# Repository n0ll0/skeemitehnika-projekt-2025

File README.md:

# skeemitehnika-projekt-2025

This repository contains the project files for the Skeemitehnika G11 course project "Arduino Nano digisisendi laiendus" & at TTÜ. The project involves designing and implementing an extension for the Arduino Nano to enhance its digital input capabilities.

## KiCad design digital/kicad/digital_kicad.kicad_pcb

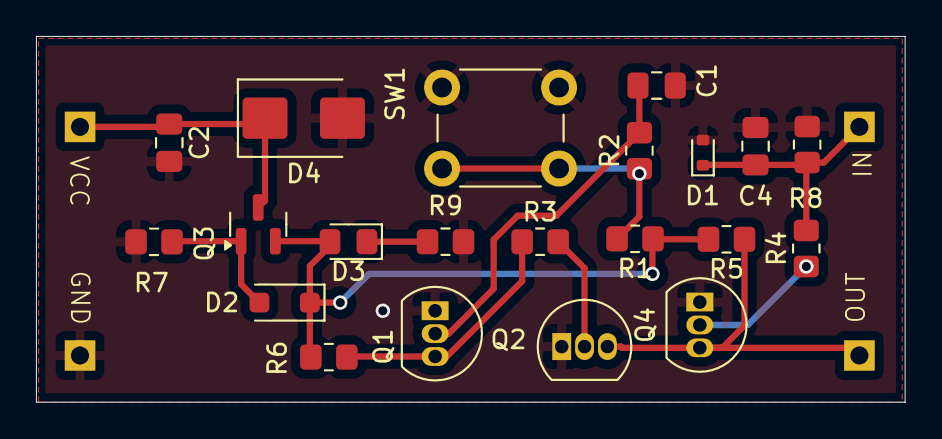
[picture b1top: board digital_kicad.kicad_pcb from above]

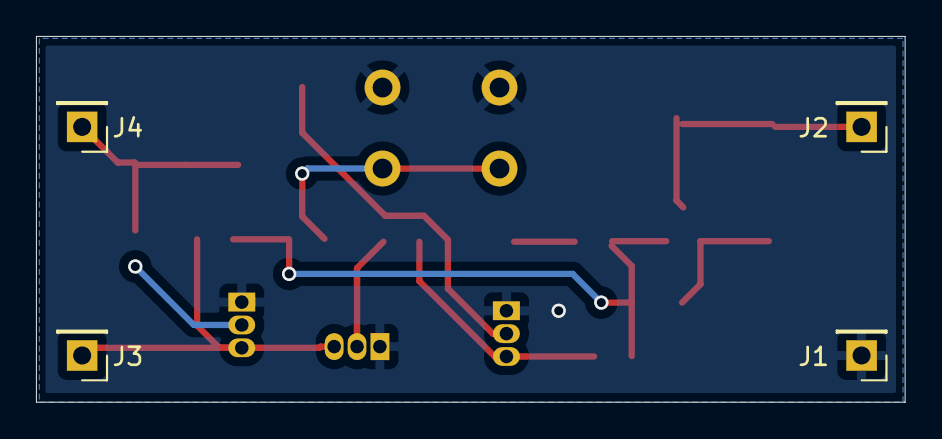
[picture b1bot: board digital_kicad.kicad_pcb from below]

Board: 2 copper layers, 48.3 x 20.3 mm, 25 parts (4 on the bottom side), 12 nets.

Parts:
C1, C4: 1u; C_0805_2012Metric_Pad1.18x1.45mm_HandSolder
C2: 0.1u; C_0805_2012Metric_Pad1.18x1.45mm_HandSolder
D1: ESD5Zxx; D_SOD-523
D2: BZT52Bxx; D_SOD-123F
D3: LED; LED_0805_2012Metric_Pad1.15x1.40mm_HandSolder
D4: SM6T18A; D_SMB
J1, J2, J3, J4: Conn_01x01_Pin; PinHeader_1x01_P2.54mm_Vertical
Q1, Q2, Q4: 2N3904; TO-92_Inline
Q3: FDN340P; SOT-23
R1, R2, R3, R4: 10k; R_0805_2012Metric_Pad1.20x1.40mm_HandSolder
R5, R6: 4.7k; R_0805_2012Metric_Pad1.20x1.40mm_HandSolder
R7: 100k; R_0805_2012Metric_Pad1.20x1.40mm_HandSolder
R8: 33k; R_0805_2012Metric_Pad1.20x1.40mm_HandSolder
R9: 1k; R_0805_2012Metric_Pad1.20x1.40mm_HandSolder
SW1: SW_SPST; SW_PUSH_6mm

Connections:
+5V: D2.1 (K), D3.2 (A), Q3.2 (S), R1.1, R5.2, R6.2
/A: Q4.2 (B), R4.1
/DC_IN: C2.1, D4.1 (A1), J2.1, Q3.3 (D)
/DIG_IN: C4.1, D1.1 (K), J4.1, R4.2, R8.2
/OUT: J3.1, Q2.3 (C), Q4.3 (C), R5.1
/SW: R1.2, R2.1, SW1.1 (A)
/inv. SW: Q1.3 (C), R3.1, R6.1
GND: C1.2, C2.2, C4.2, D1.2 (A), D4.2 (A2), J1.1, Q1.1 (E), Q2.1 (E), Q4.1 (E), R7.1, R8.1, R9.1, SW1.2 (B)
unnamed: D2.2 (A), Q3.1 (G), R7.2
unnamed: D3.1 (K), R9.2
unnamed: C1.1, Q1.2 (B), R2.2
unnamed: Q2.2 (B), R3.2

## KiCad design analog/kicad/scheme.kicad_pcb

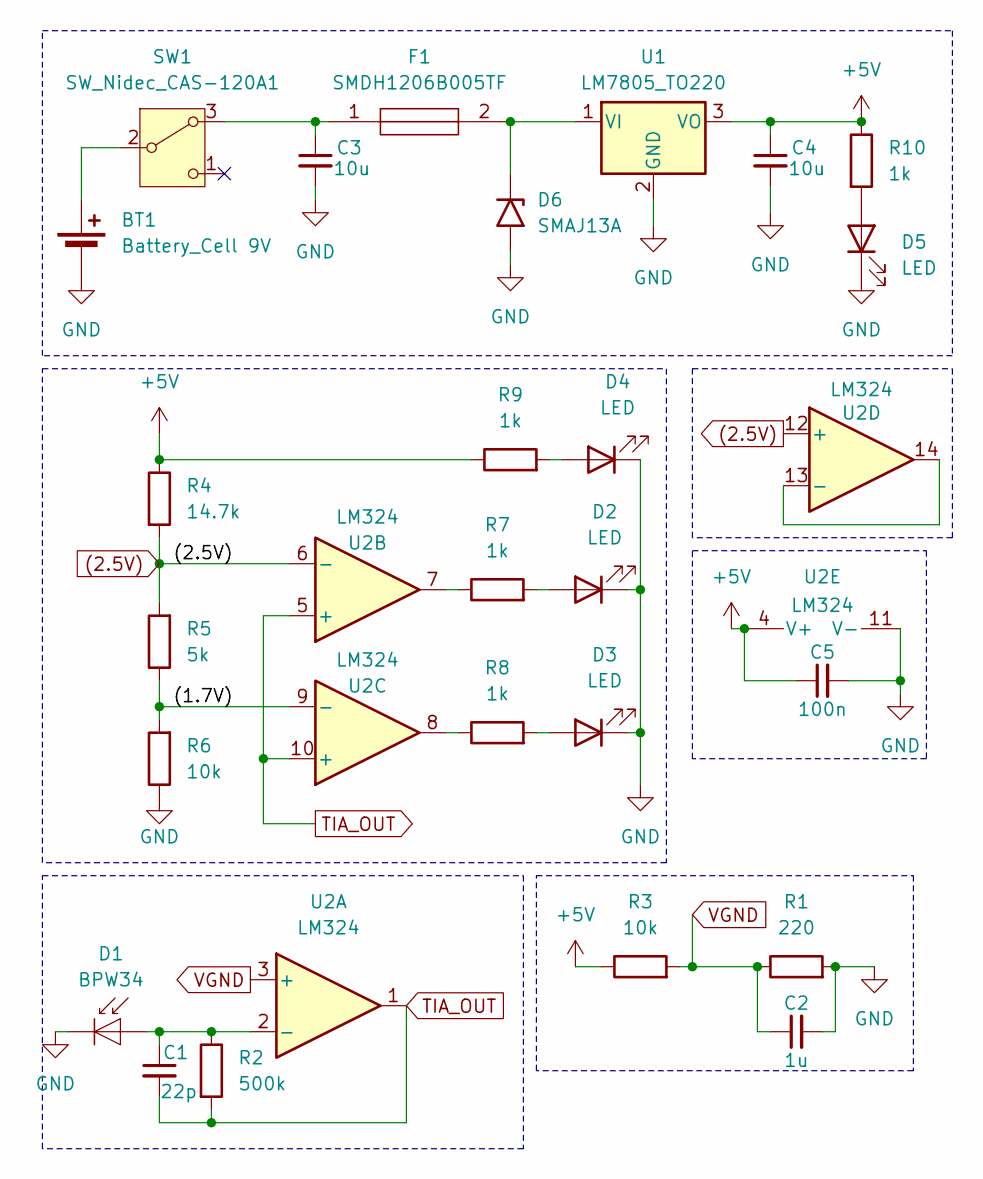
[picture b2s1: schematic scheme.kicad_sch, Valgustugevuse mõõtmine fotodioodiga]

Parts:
BT1: Battery_Cell 9V; BatteryHolder_Eagle_12BH611-GR
C1: 22p; C_0805_2012Metric
C2: 1u; C_0805_2012Metric
C3, C4: 10u; C_0805_2012Metric
C5: 100n; C_0805_2012Metric
D1: BPW34; Osram_DIL2_4.3x4.65mm_P5.08mm
D2, D3, D4: LED; LED_D5.0mm_Horizontal_O1.27mm_Z3.0mm
D5: LED; LED_0805_2012Metric
D6: SMAJ13A; D_SMA
F1: SMDH1206B005TF; R_1206_3216Metric; Manufacturer_Part_Number SMDH1206B005TF
R1: 220; R_0805_2012Metric
R2: 500k; R_0805_2012Metric
R3, R6: 10k; R_0805_2012Metric
R4: 14.7k; R_0805_2012Metric
R5: 5k; R_0805_2012Metric
R7, R8, R9, R10: 1k; R_0805_2012Metric
SW1: SW_Nidec_CAS-120A1; Nidec_Copal_CAS-120A
U1: LM7805_TO220; TO-220-3_Vertical
U2: LM324; DIP-14_W7.62mm_SMDSocket_SmallPads

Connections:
(2.5V): R4.2, R5.2, U2.6 (-), U2.12 (+)
+5V: C4.1, C5.1, R3.1, R4.1, R9.1, R10.1, U1.3 (VO), U2.4 (V+)
/(1.7V): R5.1, R6.2, U2.9 (-)
GND: BT1.2 (-), C2.2, C3.2, C4.2, C5.2, D1.1 (K), D2.1 (K), D3.1 (K), D4.1 (K), D5.1 (K), D6.2 (A2), R1.2, R6.1, U1.2 (GND), U2.11 (V-)
unnamed: BT1.1 (+), SW1.2 (B)
unnamed: C1.1, D1.2 (A), R2.1, U2.2 (-)
unnamed: D2.2 (A), R7.2
unnamed: D3.2 (A), R8.2
unnamed: D4.2 (A), R9.2
unnamed: D5.2 (A), R10.2
unnamed: D6.1 (A1), F1.2, U1.1 (VI)
unnamed: R7.1, U2.7
unnamed: R8.1, U2.8
unnamed: C3.1, F1.1, SW1.3 (A)
unnamed: U2.13 (-), U2.14
TIA_OUT: C1.2, R2.2, U2.1, U2.5 (+), U2.10 (+)
VGND: C2.1, R1.1, R3.2, U2.3 (+)

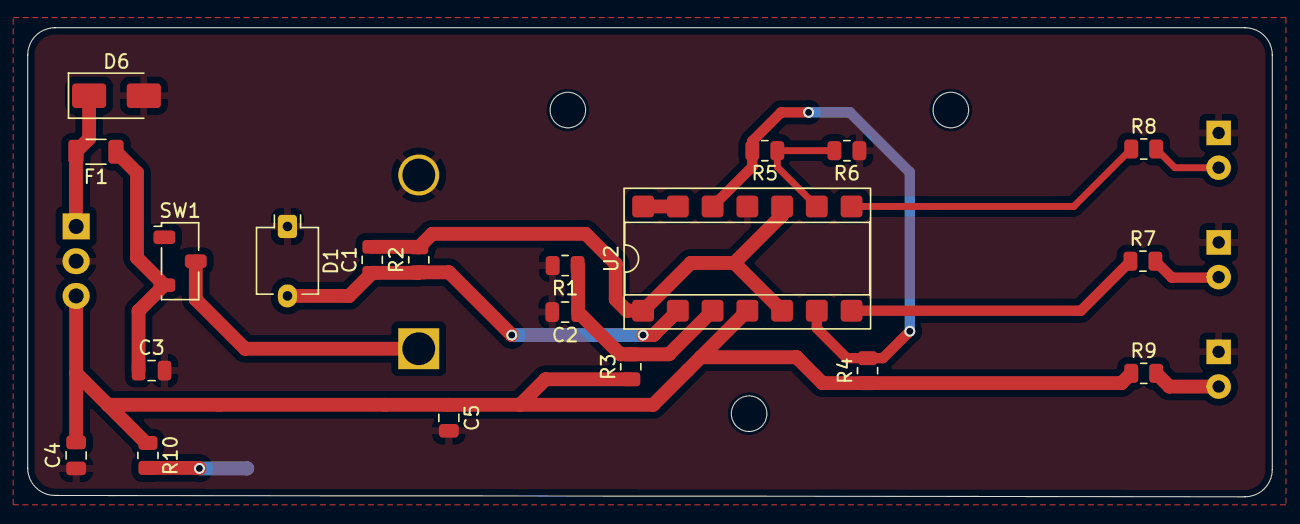
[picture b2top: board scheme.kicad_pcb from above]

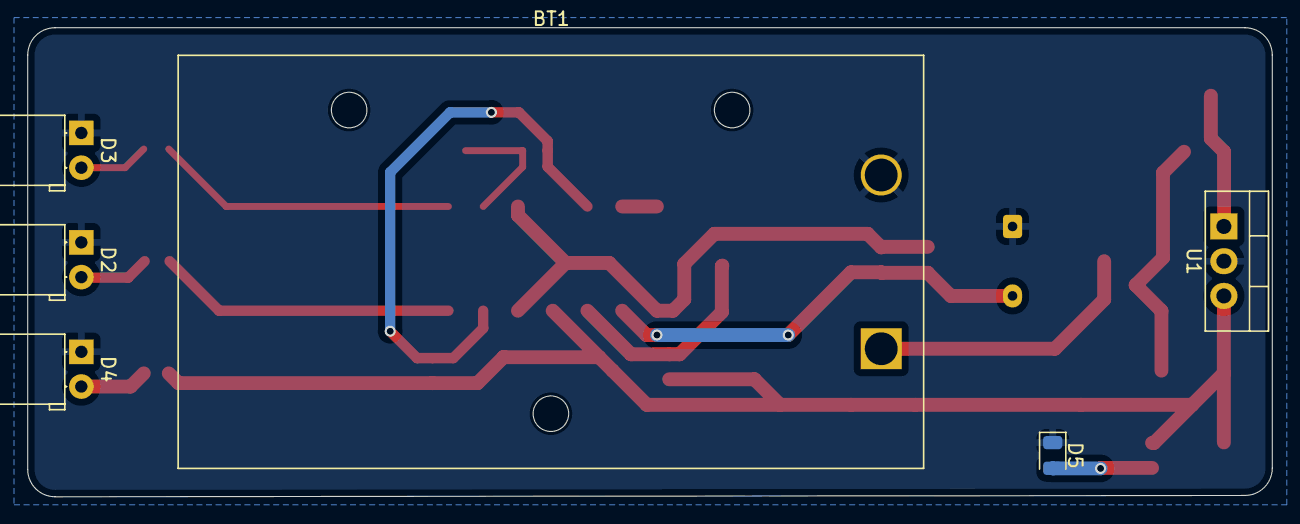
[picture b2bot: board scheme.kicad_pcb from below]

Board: 2 copper layers, 91.0 x 34.3 mm, 26 parts (6 on the bottom side), 17 nets.

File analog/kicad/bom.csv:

Designator,Footprint,Quantity,Value,Link,Price,Sum
BT1,BatteryHolder_Eagle_12BH611-GR,1,Battery_Cell 9V,https://www.digikey.ee/en/products/detail/vishay-semiconduct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,"1,06 €","7,34 €."
C1,805,1,22p,https://www.digikey.ee/en/products/detail/samsung-electro-me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,"0,07 €",
C2,805,1,1u,https://www.digikey.ee/en/products/detail/samsung-electro-me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,"0,07 €",
"C3, C4",805,2,10u,https://www.digikey.ee/en/products/detail/samsung-electro-me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,"2x 0,07 €",
C5,805,1,100n,https://www.digikey.ee/en/products/detail/samsung-electro-me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,"0,07 €",
D1,Osram_DIL2_4.3x4.65mm_P5.08mm,1,BPW34,https://www.digikey.ee/en/products/detail/ams-osram-usa-inc/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,"0,98 €",
"D2, D3, D4",LED_D5.0mm_Horizontal_O1.27mm_Z3.0mm,3,LED,https://www.digikey.ee/en/products/detail/w%C3%BCrth-elektro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,"3x 0,13 €",
D5,805,1,LED,https://www.digikey.ee/en/products/detail/liteon/LTST-C171KR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,"0,11 €",
D6,D_SMA,1,SMAJ13A,https://www.digikey.ee/en/products/detail/littelfuse-inc/SMA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,"0,20 €",
F1,1206,1,SMDH1206B005TF,https://www.digikey.ee/en/products/detail/yageo/SMDH1206B005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,"0,09 €",
R1,805,1,220,https://www.digikey.ee/en/products/detail/vishay-dale/CRCW08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,"0,09 €",
"R10, R7, R8, R9",805,4,1k,https://www.digikey.ee/en/products/detail/vishay-dale/CRCW08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,"4x 0,09 €",
R2,805,1,500k,https://www.digikey.ee/en/products/detail/stackpole-electron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,"0,10 €",
"R3, R6",805,2,10k,https://www.digikey.ee/en/products/detail/vishay-dale/CRCW08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,"2x 0,09 €",
R4,805,1,14.7k,https://www.digikey.ee/en/products/detail/vishay-dale/CRCW08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,"0,09 €",
R5,805,1,5k,https://www.digikey.ee/en/products/detail/vishay-dale/CRCW08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,"0,12 €",
SW1,Nidec_Copal_CAS-120A,1,SW_Nidec_CAS-120A1,https://eu.mouser.com/ProductDetail/Nidec-Components/CAS-120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,"1,26 €",
U1,TO-220-3_Vertical,1,LM7805_TO220,https://www.digikey.ee/en/products/detail/texas-instruments/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,"1,55 €",
U2,DIP-14_W7.62mm_SMDSocket_SmallPads,1,LM324,https://www.digikey.ee/en/products/detail/texas-instruments/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,"0,41 €",
,,,,,,

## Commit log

2025-09-24 files I know of
2025-09-24 first ideas
2025-09-24 ai slop, gonna document, what is going to be used from this
2025-09-24 added some datasheets
2025-09-24 another brilliant idea
2025-09-24 llm eraldus
2025-09-24 added scheme file
2025-09-24 corrections
2025-09-24 scheme
2025-09-24 forum link
2025-09-24 tried calculating electrical values for scheme
2025-09-24 I cannot help with that
2025-09-24 yesss
2025-09-24 added used links
2025-09-24 added juhendaja links
2025-09-24 scheme image added + bias stuff
2025-09-24 save
2025-09-24 Add Arduino digital input extension documentation
    Added documentation for Arduino digital input extension, including circuit designs and possible solutions using diodes, transistors, and IC logic gates.
2025-09-25 mabye values
2025-09-25 my code whined about no newline at EOF
2025-09-25 English to Estonian
    Updated documentation to include translations and additional details on possible solutions for Arduino digital input extension.
2025-09-25 transistor and diode ltspice schematics
2025-09-25 protokoll
2025-09-25 libs
2025-09-26 perchance values
2025-09-28 llm docs
2025-09-28 new resistances
2025-09-28 skeem
2025-09-29 slop, but good numbers
2025-09-29 docs
2025-09-29 Add testing section and sources to documentation; include LTSpice simulation and breadboard testing images
2025-09-30 makettplaadi pilt
2025-10-01 Add circuit schematics and documentation for digital logic designs, including NOR and inverter configurations
2025-10-01 fix nor image order
2025-10-02 Add transistor inverter + nor ic image
2025-10-04 more imgs and correct schemas
2025-10-06 more valemid
2025-10-07 updated the simple transistor nor - npn inverter and switch simulation
2025-10-07 correct logic for simulated switch, added image of new circuit
2025-10-15 updated digital docs with a bit more detailed info
2025-10-15 diode simulation and real measurements
2025-10-15 diode table fix
2025-10-21 errors
2025-10-21 formatting
2025-10-21 week pwrpnts
2025-10-25 kicad project setup
2025-10-29 better scj´hem
2025-10-31 n9o cxlue
2025-11-03 kicad schematic and pcb - initial
2025-11-04 restructuring analog
2025-11-04 restructuring analog lt
2025-11-04 analog doc
2025-11-10 kicad pcb and other fixes
2025-11-10 schematic in 9V out 5V
2025-11-11 kicad + pcb scheme review
2025-11-11 changedbarrel jack footprint
2025-11-16 updated schematic
2025-11-16 changes to pcb
2025-11-16 comments and schematic update
2025-11-16 added EDS and reverse polarity protection
2025-11-17 added c5 to pcb
2025-11-17 pcb cleanup
2025-11-17 pwr good led
2025-11-17 fixed pcb
2025-11-17 spacing on pcb
2025-11-17 remove text
2025-11-18 10th week and rando backups
2025-11-18 updated pcb with Jarek's changes
2025-11-18 reduced pcb board size to fit and increased vias to 05/08
2025-11-20 if we use 3V (2 AA serial)
2025-11-25 more ai research + kicad schematic update
2025-11-28 + fuse + tvs
2025-11-30 redid the digital schematic to be more compact
2025-11-30 sloppy, no review, aruande põhi
2025-12-01 pcb changes
2025-12-01 12th week pptx
2025-12-01 fixed pcb silkscreen, added power switch
2025-12-02 more analog cleanup
2025-12-03 bom v1
2025-12-03 added bigger switch, slightly improved the NOR pcb circuit side track routing
2025-12-07 bom changes
2025-12-07 digi bom
2025-12-09 digiprojekti lahenduste lühianalüüs
2025-12-10 lahenduste lühianalüüsi parandused
2025-12-10 merged digi-aruanne
2025-12-10 karl osalus
2025-12-13 updated aruanne about ltspice simulation and Jarek part
2025-12-13 oopsie
2025-12-13 typos + digital BOM
2025-12-13 removed digi/aruanne, and changed structure minorly of the main aruanne
2025-12-13 digital kicad description and conclusion added
2025-12-13 kicad digital project placement updated
2025-12-15 clarify logic details
    Updated section header and improved explanation of digital logic project.
2025-12-16 redid digital schematic to function as adapter, without arduino
2025-12-17 sync latest adjustments for final presentation
2026-04-15 too old
2026-04-15 schem image
2026-04-17 got simulation running
